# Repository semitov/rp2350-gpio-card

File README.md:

# rp2350-gpio-card
Expansion Card circuit based on RP2350 for Framework mainboards providing GPIO to the computer. Circuit is based on [Expansion Card template](https://github.com/FrameworkComputer/ExpansionCards) and [RP2350A Minimal board](https://datasheets.raspberrypi.com/rp2350/hardware-design-with-rp2350.pdf). Designed in [KiCad](https://www.kicad.org/). It got produced and assembled. Its fully functional.

## Gallery
* Render of card with Molex 1054440011 (Framework template)

* Render of card with TYPEC-950-ARP24 (NextPCB template)

## GPIO
### Front
| Label | Name   | SPI       | UART       | I2C        | ADC |
| :---- | :----- | :-------- | :--------- | :--------- | :-- |
| 0     | GPIO0  | SPI0 RX   | UART0 TX   | I2C0 SDA   |     |
| 1     | GPIO1  | SPI0 CSn  | UART0 RX   | I2C0 SCL   |     |
| 2     | GPIO2  | SPI0 SCK  |            | I2C1 SDA   |     |
| 3     | GPIO3  | SPI0 TX   |            | I2C1 SCL   |     |
| 4     | GPIO4  | SPI0 RX   | UART1 TX   | I2C0 SDA   |     |
| 5     | GPIO5  | SPI0 CSn  | UART1 RX   | I2C0 SCL   |     |
| 6     | GPIO6  | SPI0 SCK  |            | I2C1 SDA   |     |
| 7     | GPIO7  | SPI0 TX   |            | I2C1 SCL   |     |
| VCC   | 3.3v   |           |            |            |     |
| R     | Reset  |           |            |            |     |

### Back
| Label | Name   | SPI       | UART       | I2C        | ADC   |
| :---- | :----- | :-------- | :--------- | :--------- | :---- |
| 29    | GPIO29 |           |            |            | ADC3  |
| 28    | GPIO28 |           |            |            | ADC2  |
| 27    | GPIO27 |           |            | I2C1 SDL   | ADC1  |
| G     | Ground |           |            |            |       |
| 13    | GPIO13 | SPI1 CSN  | UART0 RX   | I2C0 SCL   |       |
| 12    | GPIO12 | SPI1 RX   | UART0 TX   | I2C0 SDA   |       |
| 11    | GPIO11 | SPI1 TX   |            | I2C1 SCL   |       |
| 10    | GPIO10 | SPI1 SCK  |            | I2C1 SDA   |       |
| 9     | GPIO9  | SPI1 CSn  | UART1 RX   | I2C0 SCL   |       |
| B     | Boot   |           |            |            |       |

## License
Designed by: [Tan Siret Akıncı](https://github.com/tansiret).
Schematics and footprint are licensed with [CC BY 4.0](LICENSE).
Politecnico di Torino name used in this project is © 2025 Politecnico di Torino. The project is sponsored by © 2025 [DeepComputing](https://deepcomputing.io/) and © 2025 [NextPCB](https://www.nextpcb.com/).
The project has been certified by [OSHWA](https://oshwa.org/) as Open Source Hardware (UID: [IT000024](https://certification.oshwa.org/it000024.html)).
</br>

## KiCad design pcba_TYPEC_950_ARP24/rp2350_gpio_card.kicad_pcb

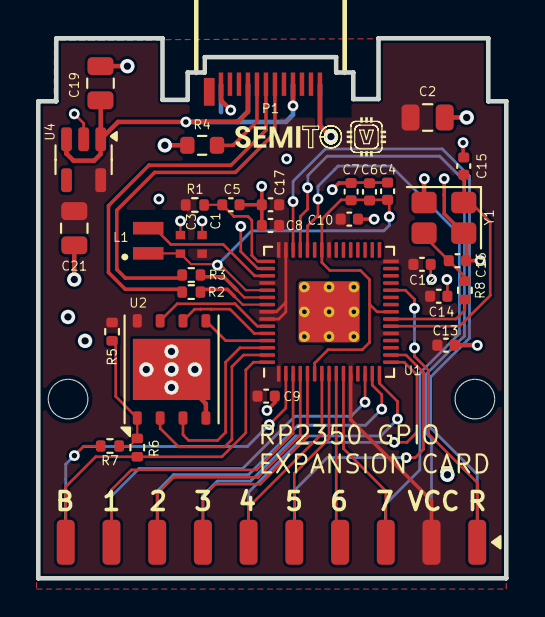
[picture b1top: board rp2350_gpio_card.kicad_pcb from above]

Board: 4 copper layers, 26.0 x 30.0 mm, 36 parts (1 on the bottom side), 38 nets.

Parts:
C1, C3: 4.7u; C_0402_1005Metric_small_pads
C2, C19, C21: 10u; C_0805_2012Metric
C4, C7, C8, C9, C10, C12, C13, C14, C17: 100n; C_0402_1005Metric
C5, C6: 4.7u; C_0402_1005Metric
C15, C16: 15p; C_0402_1005Metric
H1, H2: MountingHole; MountingHole_2.2mm_M2
J1, J2: Conn_01x10_Pin; Custom_Harwin_M20-89010xx_1x10_P2.54mm_Horizontal
L1: 3.3u; L_pol_2016
P1: USB_C_Plug_USB2.0; TYPEC-SMD_TYPEC-950-ARP24
R1: 33; R_0402_1005Metric
R2, R3: 27; R_0402_1005Metric
R4: 5.1k; R_0603_1608Metric
R5, R7: DNF; R_0402_1005Metric
R6: 0; R_0402_1005Metric
R8: 1k; R_0402_1005Metric
U1: RP2350_60QFN; RP2350-QFN-60-1EP_7x7_P0.4mm_EP3.4x3.4mm_ThermalVias
U2: W25Q128JVS; WSON-8-1EP_6x5mm_P1.27mm_EP3.4x4.3mm
U4: AP2127K-3.3; SOT-23-5
Y1: ABM8-272-T3; Crystal_SMD_3225-4Pin_3.2x2.5mm

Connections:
+1V1: C3.1, C4.1, C6.1, C7.1, L1.1, U1.6 (DVDD), U1.23 (DVDD), U1.39 (DVDD), U1.50 (VREG_FB)
+3.3V: C1.1, C2.1, C8.1, C9.1, C10.1, C12.1, C13.1, C14.1, C17.1, C21.1, J2.2, R1.1, R5.1, U1.1 (IOVDD), U1.11 (IOVDD), U1.20 (IOVDD), U1.30 (IOVDD), U1.38 (IOVDD), U1.44 (ADC_AVDD), U1.45 (IOVDD), U1.49 (VREG_VIN), U1.53 (USB_OTP_VDD), U1.54 (QSPI_IOVDD), U2.8 (VCC), U4.5 (VOUT)
/FLASH_SS: R5.2, R6.2, R7.2, U2.1 (~CS)
/GPIO0: J1.1, R7.1, U1.2 (GPIO0)
/GPIO1: J2.9, U1.3 (GPIO1)
/GPIO2: J2.8, U1.4 (GPIO2)
/GPIO3: J2.7, U1.5 (GPIO3)
/GPIO4: J2.6, U1.7 (GPIO4)
/GPIO5: J2.5, U1.8 (GPIO5)
/GPIO6: J2.4, U1.9 (GPIO6)
/GPIO7: J2.3, U1.10 (GPIO7)
/GPIO9: J1.2, U1.13 (GPIO9)
/GPIO10: J1.3, U1.14 (GPIO10)
/GPIO11: J1.4, U1.15 (GPIO11)
/GPIO12: J1.5, U1.16 (GPIO12)
/GPIO13: J1.6, U1.17 (GPIO13)
/GPIO27_ADC1: J1.8, U1.41 (GPIO27_ADC1)
/GPIO28_ADC2: J1.9, U1.42 (GPIO28_ADC2)
/GPIO29_ADC3: J1.10, U1.43 (GPIO29_ADC3)
/QSPI_SCLK: U1.56 (QSPI_SCLK), U2.6 (CLK)
/QSPI_SD0: U1.57 (QSPI_SD0), U2.5 (DI/IO_{0})
/QSPI_SD1: U1.59 (QSPI_SD1), U2.2 (DO/IO_{1})
/QSPI_SD2: U1.58 (QSPI_SD2), U2.3 (~WP/IO_{2})
/QSPI_SD3: U1.55 (QSPI_SD3), U2.7 (~HOLD/~RESET/IO_{3})
/QSPI_SS: J2.10, R6.1, U1.60 (QSPI_SS)
/RUN: J2.1, U1.26 (RUN)
/USB_D+: P1.A6 (D+), R2.1
/USB_D-: P1.A7 (D-), R3.1
/VREG_AVDD: C5.1, R1.2, U1.46 (VREG_AVDD)
/VREG_LX: L1.2, U1.48 (VREG_LX)
/XIN: C15.1, U1.21 (XIN), Y1.1
/XOUT: R8.1, U1.22 (XOUT)
GND: C1.2, C2.2, C3.2, C4.2, C5.2, C6.2, C7.2, C8.2, C9.2, C10.2, C12.2, C13.2, C14.2, C15.2, C16.2, C17.2, C19.2, C21.2, J1.7, P1.A1 (GND), P1.A12 (GND), P1.B1 (GND), P1.B12 (GND), R4.2, U1.47 (VREG_PGND), U1.61 (GND), U2.4 (GND), U2.9 (EP), U4.2 (GND), Y1.2, Y1.4
unnamed: C16.1, R8.2, Y1.3
unnamed: P1.A5 (CC), R4.1
unnamed: R3.2, U1.51 (USB_DM)
unnamed: R2.2, U1.52 (USB_DP)
VBUS: C19.1, P1.A4 (VBUS), P1.A9 (VBUS), P1.B4 (VBUS), P1.B9 (VBUS), U4.1 (VIN), U4.3 (EN)

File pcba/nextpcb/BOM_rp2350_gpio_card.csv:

reference,value,footprint,MPN,manufacturer,Category,SKU,price,quantity
"C1,C3",4.7u,C_0402_1005Metric_small_pads,06036D475MAT2A,Kyocera,Ceramic Capacitors,-,-,2
"C5,C6",4.7u,C_0402_1005Metric,06036D475MAT2A,Kyocera,Ceramic Capacitors,-,-,2
"C9,C10,C17,C8,C12,C4,C7,C13,C14",100n,C_0402_1005Metric,06035L104K4T2A,Kyocera,Ceramic Capacitors,1009753559,0.02977,9
"C15,C16",15p,C_0402_1005Metric,VJ0603A150JXBAP,Vishay,Ceramic Capacitors,-,-,2
"C19,C2,C21",10u,C_0805_2012Metric,UMK325BJ106KM-T,Taiyo Yuden,Ceramic Capacitors,2500324717,0.13001,3
"H1,H2",MountingHole,MountingHole_2.2mm_M2,,,,,,2
"J2,J1",Conn_01x10_Pin,Custom_Harwin_M20-89010xx_1x10_P2.54mm_Horizontal,DNP ! DO NOT PLACE,,,-,-,-
L1,3.3u,L_pol_2016,B32926C3335M000,TDK,Capacitors,-,-,1
P1,USB_C_Plug_USB2.0,USB_C_Plug_Molex_105444,USB2.0-AB06,Panasonic,Tools and Supplies,-,-,1
R1,33,R_0402_1005Metric,XF2M-3315-1A,Omron,FFC / FPC,1027849864,0.39157,1
"R3,R2",27,R_0402_1005Metric,2-84953-7,TE Connectivity (Tyco Electronics),FFC / FPC,-,-,2
R4,5.1k,R_0603_1608Metric,CRCW04025K10JNED,Vishay,Chip SMD Resistors,1007326799,0.00657,1
"R5,R7",DNF,R_0402_1005Metric,STS4DNF60L,STMicroelectronics,MOSFETs,1018687185,0.28249,2
R6,0,R_0402_1005Metric,CR0603-J/-000ELF,Bourns,Chip SMD Resistors,-,-,1
R8,1k,R_0402_1005Metric,CR1206-FX-1001ELF,Bourns,Chip SMD Resistors,1002726470,0.01646,1
U1,RP2350_60QFN,RP2350-QFN-60-1EP_7x7_P0.4mm_EP3.4x3.4mm_ThermalVias,RP2350A,Raspberry Pi,Chip Microcontrollers,,,1
U2,W25Q128JVS,WSON-8-1EP_6x5mm_P1.27mm_EP3.4x4.3mm,W25Q128JVSIQ,Winbond Electronics,FLASH,1003909429,1.24697,1
U4,AP2127K-3.3,SOT-23-5,AP2127K-1.8TRG1,Diodes,"Linear Voltage Regulators, LDO",2500317187,0.12386,1
Y1,ABM8-272-T3,Crystal_SMD_3225-4Pin_3.2x2.5mm,RDE5C1H272J0S1H03A,Murata,Ceramic Capacitors,-,-,1

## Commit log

2025-08-04 initial commit with first version of schematics
2025-08-04 update schematics and start working on pcb (very WIP, need help)
2025-08-06 finish first PCB prototype, modify schematic
2025-08-06 add personal note
2025-08-06 update fillings
2025-08-06 add silkscreen logos and stuff
2025-08-06 minor changes
2025-08-07 change footprint, version v122
2025-08-07 update photo
2025-08-07 green pcb
2025-08-10 purple pcb
2025-08-11 add copyright claim
2025-08-11 proper copyright notice
2025-08-21 update design
2025-08-22 version 1.2.4 - fix floating pads and some errors
2025-08-22 edit readme and re-render images
2025-08-24 version 1.3.0 - major fixes for floating pins
2025-08-24 version 1.3.1 - thermal fix, new render
2025-08-24 edit silkscreen
2025-08-24 render
2025-08-24 fix all floating errors
2025-08-24 version v132
2025-08-24 minor trace edit
2025-08-24 fix usb connection issues
2025-08-29 add OSHW certification
2025-08-29 correct link
2025-08-29 add GPIO table (thanks Mr_Bonce)
2025-08-29 edit pcb
2025-08-29 edit readme
2025-09-03 update board, add NextPCB silkscreen, add sponsors to the readme
2025-09-09 minor touches
2025-09-09 fix inductor magnetism issue and rearrange several other components according to RP2350 datasheet
2025-09-10 2 layer gerber and minor fix
2025-09-10 add no fill zone to L1
2025-09-11 version 1.3.5 - fix impedance mismatch at usb and improve design
2025-09-11 gerbers
2025-09-11 small silkscreen edit
2025-09-17 clean up and update BOM/pos files
2025-09-18 switch to solid connection rather than thermal relief
2025-09-18 fix DFM
2025-09-19 version 1.3.6 - smaller edge to copper clearance and minor design changes
2025-09-19 small component placement changes
2025-09-22 add different type-c version of the board
2025-09-23 minor type-c fix

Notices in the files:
pcba_TYPEC_950_ARP24/rp2350_gpio_card.kicad_pcb:
This work is licensed under a Creative Commons Attribution 4.0 International License
License: CC BY 4.0
